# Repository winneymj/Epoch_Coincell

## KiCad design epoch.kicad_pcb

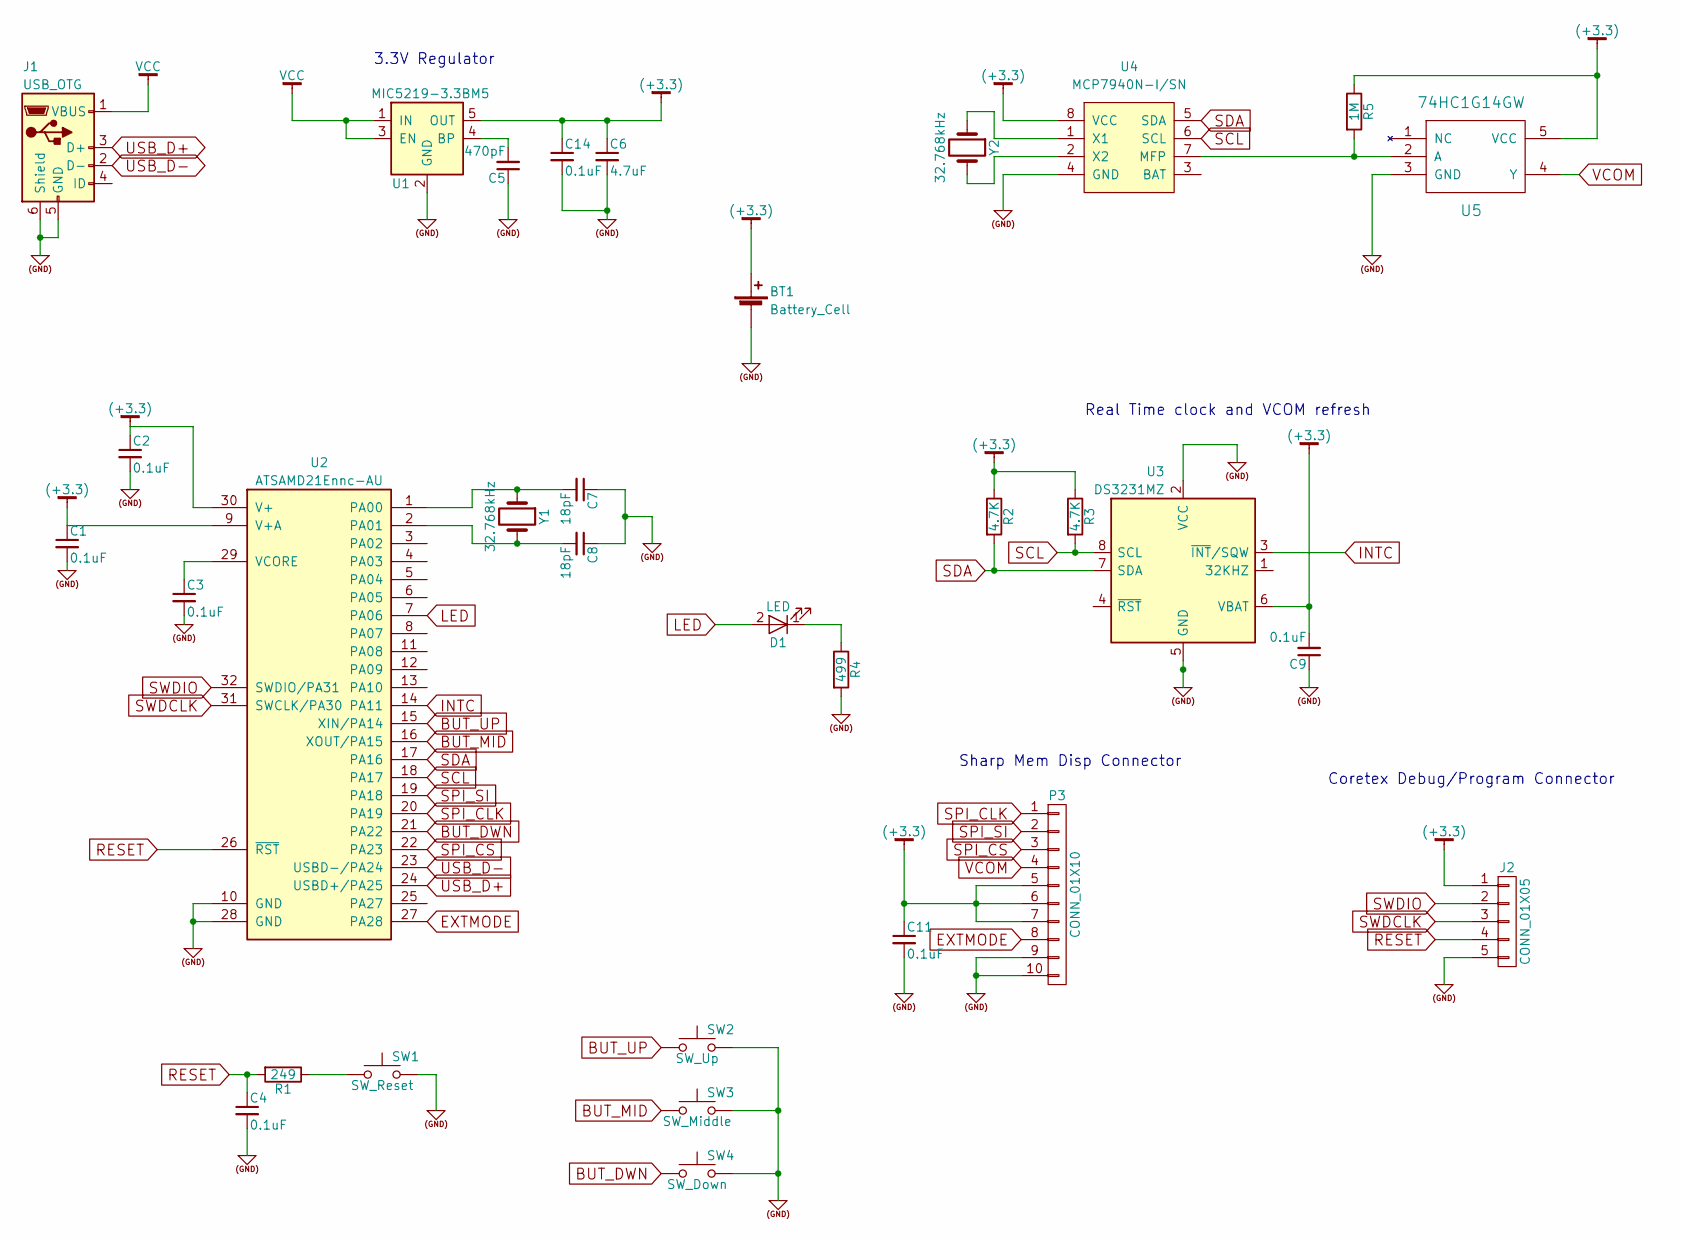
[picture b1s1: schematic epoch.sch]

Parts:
BT1: Battery_Cell; CR2032-001
C1, C2, C3, C4, C9, C11, C14: 0.1uF; C_0805_HandSoldering
C5: 470pF; C_0805_HandSoldering
C6: 4.7uF; C_0805_HandSoldering
C7, C8: 18pF; C_0805_HandSoldering
D1: LED; LED_0805
J1: USB_OTG; USB-MICROB_LARGEPAD
J2: CONN_01X05; Pin_Header_Straight_1x05_Pitch1.27mm
P3: CONN_01X10; MOLEX_0.5MM_505278
R1: 249; R_0805_HandSoldering
R2, R3: 4.7K; R_0805_HandSoldering
R4: 499; R_0805_HandSoldering
R5: 1M; R_0805_HandSoldering
SW1: SW_Reset; SW_SPST_B3U-1100P
SW2: SW_Up; SW_SPST_B3U-1100P
SW3: SW_Middle; SW_SPST_B3U-1100P
SW4: SW_Down; SW_SPST_B3U-1100P
U1: MIC5219-3.3BM5; SOT-23-5
U2: ATSAMD21Ennc-AU; TQFP-32_7x7mm_Pitch0.8mm; MPN ATSAMD21Ennc-AU
U3: DS3231MZ; SOIC-8_3.9x4.9mm_Pitch1.27mm
U4: MCP7940N-I/SN; SOIC-8_3.9x4.9mm_Pitch1.27mm; MPN MCP7940N-I/SN
U5: 74HC1G14GW; SOT-353_SC-70-5_Handsoldering
Y1, Y2: 32.768kHz; Crystal_SMD_EuroQuartz_EQ161-2pin_3.2x1.5mm

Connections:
(+3.3): BT1.1 (+), C1.1, C2.1, C6.1, C9.2, C11.1, C14.1, J2.1, P3.5, P3.6, P3.7, R2.1, R3.1, R5.1, U1.5 (OUT), U2.9 (V+A), U2.30 (V+), U3.6 (VBAT), U4.8 (VCC), U5.5 (VCC)
(GND): BT1.2 (-), C1.2, C2.2, C3.2, C4.2, C5.1, C6.2, C7.1, C8.1, C9.1, C11.2, C14.2, J1.5 (GND), J1.6 (Shield), J2.5, P3.9, P3.10, R4.2, SW1.2, SW2.2, SW3.2, SW4.2, U1.2 (GND), U2.10 (GND), U2.28 (GND), U3.2 (VCC), U3.5 (GND), U4.4 (GND), U5.3 (GND)
BUT_DWN: SW4.1, U2.21 (PA22)
BUT_MID: SW3.1, U2.16 (XOUT/PA15)
BUT_UP: SW2.1, U2.15 (XIN/PA14)
EXTMODE: P3.8, U2.27 (PA28)
INTC: U2.14 (PA11), U3.3 (~INT~/SQW)
LED: D1.2 (A), U2.7 (PA06)
unnamed: C3.1, U2.29 (VCORE)
unnamed: C5.2, U1.4 (BP)
unnamed: C7.2, U2.1 (PA00), Y1.1
unnamed: C8.2, U2.2 (PA01), Y1.2
unnamed: D1.1 (K), R4.1
unnamed: R1.1, SW1.1
unnamed: R5.2, U4.7 (MFP), U5.2 (A)
unnamed: U4.1 (X1), Y2.1
unnamed: U4.2 (X2), Y2.2
RESET: C4.1, J2.4, R1.2, U2.26 (~RST)
SCL: R3.2, U2.18 (PA17), U3.8 (SCL), U4.6 (SCL)
SDA: R2.2, U2.17 (PA16), U3.7 (SDA), U4.5 (SDA)
SPI_CLK: P3.1, U2.20 (PA19)
SPI_CS: P3.3, U2.22 (PA23)
SPI_SI: P3.2, U2.19 (PA18)
SWDCLK: J2.3, U2.31 (SWCLK/PA30)
SWDIO: J2.2, U2.32 (SWDIO/PA31)
USB_D+: J1.3 (D+), U2.24 (USBD+/PA25)
USB_D-: J1.2 (D-), U2.23 (USBD-/PA24)
VCC: J1.1 (VBUS), U1.1 (IN), U1.3 (EN)
VCOM: P3.4, U5.4 (Y)

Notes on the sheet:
Coretex Debug/Program Connector
3.3V Regulator
Sharp Mem Disp Connector
Real Time clock and VCOM refresh

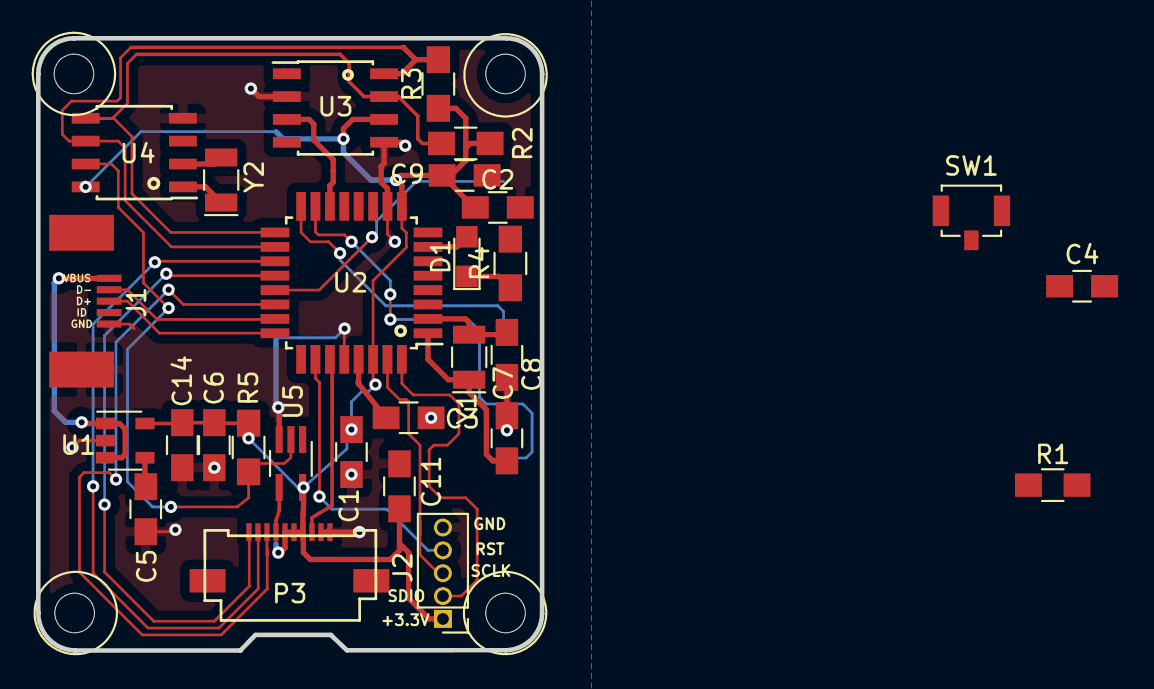
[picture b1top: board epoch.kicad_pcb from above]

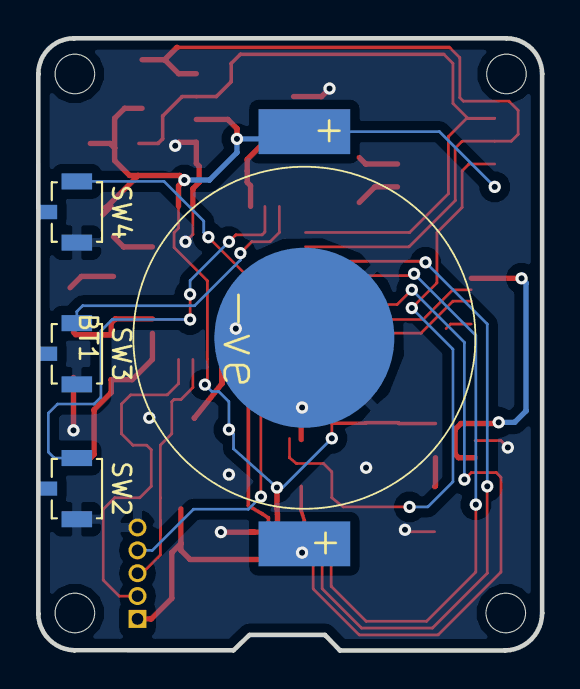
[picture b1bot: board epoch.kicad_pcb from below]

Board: 2 copper layers, 28.0 x 34.0 mm, 32 parts (4 on the bottom side), 29 nets.

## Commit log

2017-04-17 Link buttons and add PCB
2017-04-18 More Layout
2017-04-19 Start connecting
2017-04-21 Add coincell
2017-04-22 Battery parts
2017-04-23 More connections and change battery to pads
2017-04-25 Complete connections
2017-04-27 Add LIPO charging
2017-04-29 More connections
2017-04-29 Rework using coincell and 2 RTC chips
2017-04-30 Wire up
2017-05-02 Update resonator crystal to 18pF and create BOM csv
2017-05-04 Place drill holes.
2017-05-05 Round corners and add LED
2017-05-06 Route LED
